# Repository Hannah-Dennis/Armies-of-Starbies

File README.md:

# Armies-of-Starbies

## About my Starbie:

My Starbie is a tiny handheld pet inspired by The Amazing World of Gumball's episode: The Console. Instead of the guide's star shape, I designed my PCB as a rounded rectangular board with a direction pad, a "Player HD" logo (my username sometimes) under the screen, and a cool pattern at the back of the circuit board.

It runs on a XIAO ESP32-C3 and has:
- A 0.96" OLED screen where my pet lives.
- An MPU6050 motion sensor so the pet reacts when you move it.
- A DHT11 sensor that measures temperature and humidity.
- A custom 32x32 pixel sprite that I drew myself.

# Controls

| Control | What it does |
|---|---|
| Button 1 (SW1) | Opens the action menu. Press again to choose the highlighted action. |
| Tilt (in the menu) | Rolls the ball toward an action: up = NAP, right = PLAY, down = FEED, left = PET |
| Button 2 (SW2) | Shows or hides the stats screen (Joy, Energy, Fullness, temperature and humidity) |
| Shake | Wakes the pet if it's napping, and gives it a little boost of joy |

# Actions

| Action | What happens | Stats |
|---|---|---|
| NAP | The pet sleeps for 48 seconds with floating Zs | Energy ↑↑, Fullness ↓ |
| PLAY | The pet runs two fast laps, with hearts | Joy ↑↑, Energy ↓, Fullness ↓ |
| FEED | The pet wiggles and jumps | Fullness ↑↑ |
| PET | The pet jumps and shows hearts | Joy ↑ |

When you're not doing anything, the pet wanders across the screen with a
little sparkle behind it.

# What I used:
- KiCad's PCB editor
- KiCad's Schematic editor
- Piskel (to make sprite)
- Image2cpp

# Images:

# Sprite I made:

# BOM Table:
|Item|Qty|Supplier|Cost/item|Total Cost|link|
|----|---|--------|---------|----------|----|
|XIAO ESP32 C3|1|Seeedstudio|$4.90|$4.90|https://www.seeedstudio.com/Seeed-XIAO-ESP32C3-p-5431.html|
|0.96 OLED|1|Amazon|$5.99|$5.99|https://www.amazon.com/dp/B0GBVWBWCR|
|MPU6050|1|Amazon|$2.19|$2.19|https://www.amazon.com/dp/B0943SGP34|
|DHT11|1|Amazon|$3.78|$3.78|https://www.amazon.com/dp/B0BLG7R99R|
|MX Switches|1|Amazon|$4.99|$4.99|https://www.amazon.com//dp/B0FQP8VYX4|
|Keycaps|1|Amazon|$2.88|$2.88|https://www.amazon.com/dp/B0CQ2VLMVY|
|PCB|1|JLCPCB|$7.36|$7.36|https://www.jlcpcb.com/|
|Estimated total|1|-|-|$32.09|-|

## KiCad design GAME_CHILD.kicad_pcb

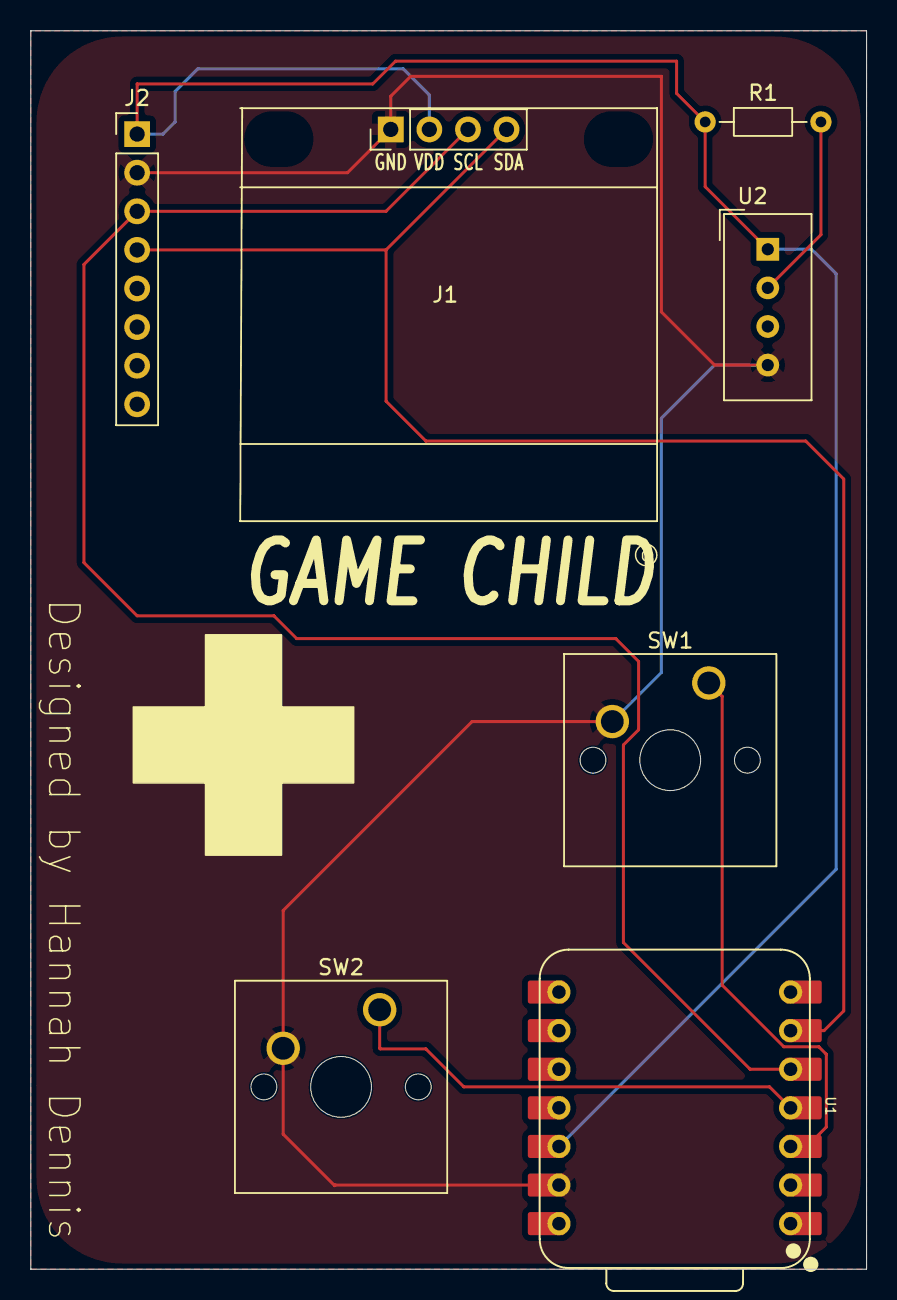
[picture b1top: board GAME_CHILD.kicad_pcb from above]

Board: 2 copper layers, 55.0 x 81.5 mm, 7 parts (0 on the bottom side), 7 nets.

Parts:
J1: Conn_01x04_Pin; Display_128x64_096_I2C
J2: Conn_01x08_Pin; PinHeader_1x08_P2.54mm_Vertical
R1: R; R_Axial_DIN0204_L3.6mm_D1.6mm_P7.62mm_Horizontal
SW1, SW2: SW_Push; SW_Cherry_MX_1.00u_PCB
U1: XIAO-ESP32-C3-SMD; XIAO-ESP32-C6-DIP
U2: DHT11; Aosong_DHT11_5.5x12.0_P2.54mm

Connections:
+3.3V: J1.2, J2.1, R1.1, U1.12 (3V3_OUT), U2.1 (VDD)
/DHT11 DATA: R1.2, U2.2 (DATA)
/GPIO2: SW1.1, U1.3 (D2)
/GPIO3: SW2.1, U1.4 (D3)
/SCL: J1.3, J2.3, U1.5 (D4)
/SDA: J1.4, J2.4, U1.6 (D5)
GND: J1.1, J2.2, SW1.2, SW2.2, U1.13 (GND), U2.4 (GND)
